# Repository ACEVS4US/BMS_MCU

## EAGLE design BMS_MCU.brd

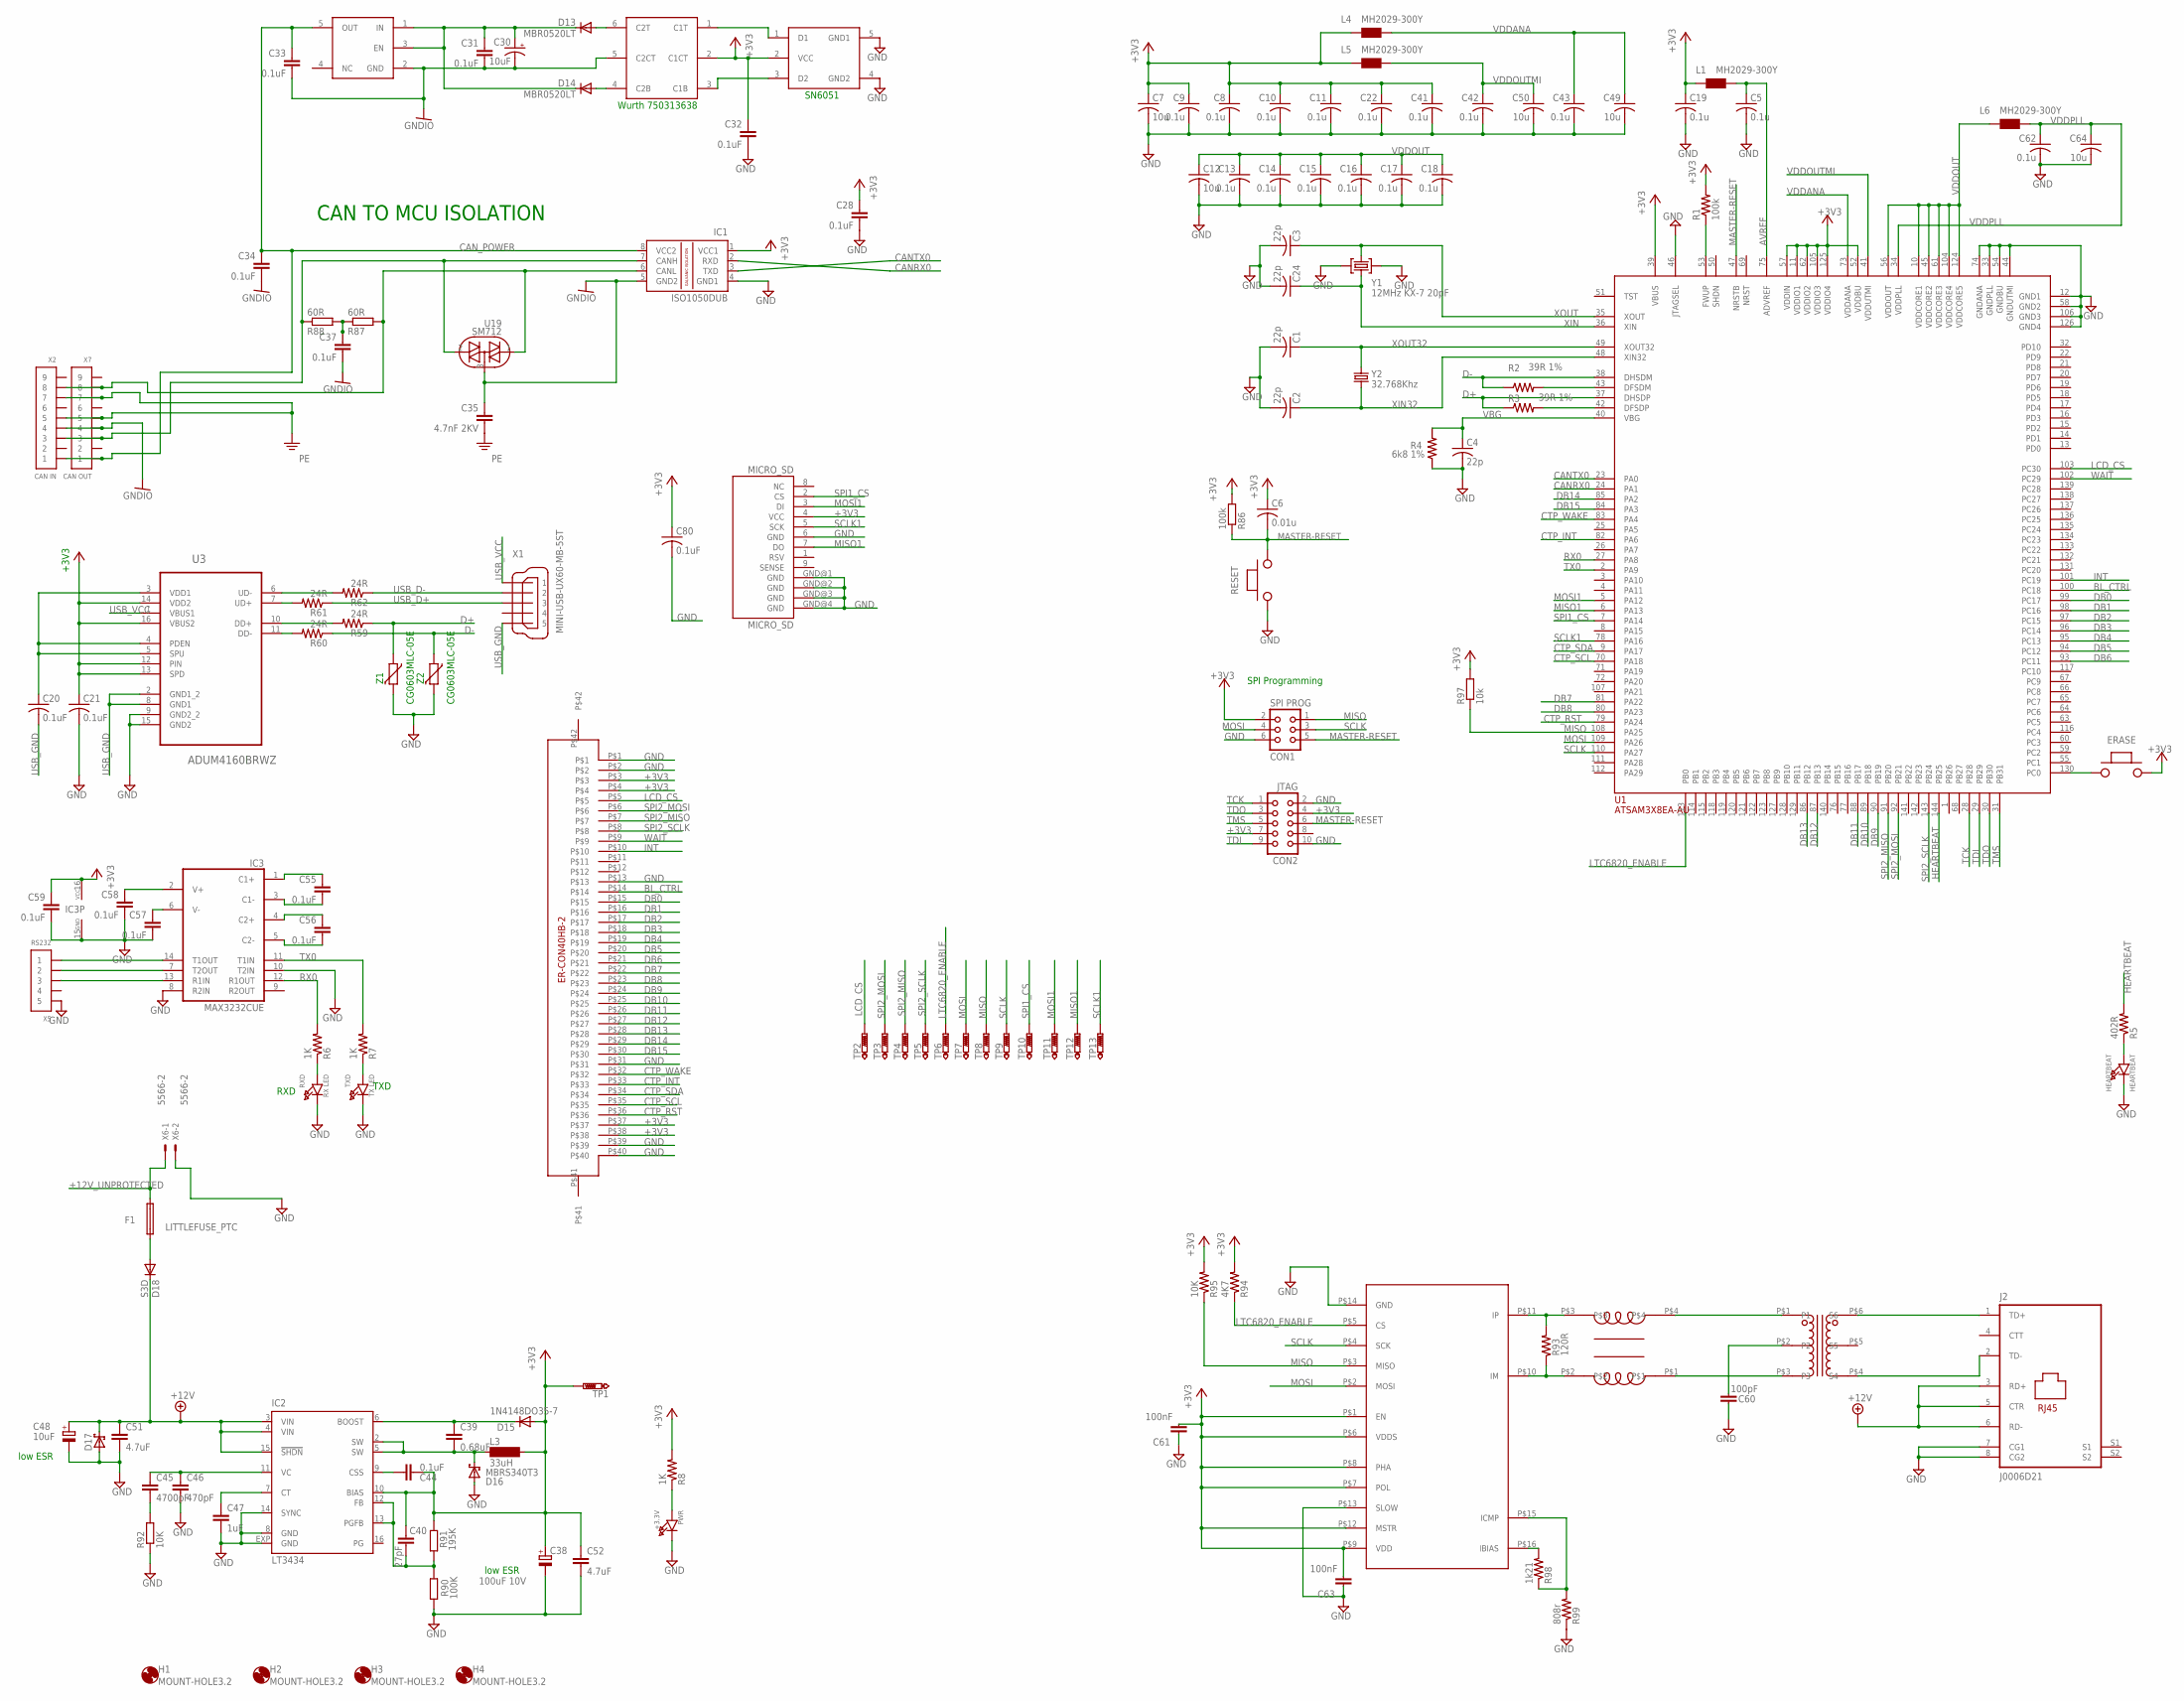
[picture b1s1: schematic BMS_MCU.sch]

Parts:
+3.3V: PWR; CHIPLED_0805
C1, C2, C4: 22p; C0805
C3, C24: 22p; C1206
C5, C8, C9, C10, C11, C13, C14, C15, C16, C17, C18, C19, C22, C41, C42, C43, C62: 0.1u; C0805
C6: 0.01u; C0805
C7, C12, C49, C50, C64: 10u; C0805
C20, C21, C28, C80: 0.1uF; C0805
C30, C48: 10uF; SMC_D
C31, C34, C44, C55, C56, C57, C58, C59: 0.1uF; C0603
C32, C33, C37: 0.1uF; C1206
C35: 4.7nF 2KV; C1206
C38: 100uF 10V; SMC_D
C39: 0.68uF; C0603
C40: 27pF; C0603
C45: 4700pF; C0603
C46: 470pF; C0603
C47: 1uF; C0603
C51, C52: 4.7uF; C1206
C60: 100pF; C1206@1
C61, C63: 100nF; C0603@1
CON1: SPI PROG; CON06
CON2: JTAG; CON10
D13, D14: MBR0520LT; SOD123
D15: 1N4148DO35-7; DO35-7
D16: MBRS340T3; SMC
D17: SCHOTTKY-DIODESMC; SMC
D18: S3D; SMC
ERASE: PUCHBUTTON
F1: LITTLEFUSE_PTC; 1812
H1, H2, H3, H4: MOUNT-HOLE3.2; 3,2
HEARTBEAT: HEARTBEAT; CHIPLED_0805
IC1: ISO1050DUB; DUB-R-PDSO-G8
IC2: LT3434; TSSOP16EXP
IC3: MAX3232CUE; TSSOP16
J2: J0006D21; J0-C/D/E
L1, L4, L5, L6: MH2029-300Y; 0805
L3: 33uH; MS85
MICRO_SD: MICRO_SD; MICROSD_PP
R1: 100k; R0805
R2, R3: 39R 1%; R0805
R4: 6k8 1%; R0805
R5: 402R; R0805
R6, R7, R8: 1K; R0805
R59, R60, R61, R62: 24R; R0805
R86: 100k; R0603
R87, R88: 60R; R0603
R90: 100K; R0603
R91: 195K; R0603
R92, R95: 10K; R0603
R93: 120R; R0603
R94: 4K7; R0603
R97: 10k; R0603
R98: 1k21; R0603
R99: 808r; R0603
RESET: PUCHBUTTON
RXD: RX LED; CHIPLED_0805
TP1, TP2, TP3, TP4, TP5, TP6, TP7, TP8, TP9, TP10, TP11, TP12, TP13: PTR1PAD1-13; P1-13
TXD: TX LED; CHIPLED_0805
U1: ATSAM3X8EA-AU; LQFP144
U2: LTC6820; MSOP16
U3: ADUM4160BRWZ; SOIC127P1032X265-16N
U16: SN6501; SOT23-DBV
U17: WURTHWURTH; TSOT23-6_DDC
U18: TPS76350; SOT23-DBV
U19: SM712; SOT23
U$1: DLW43SH510XK2; DLW43S
U$2: ER-CON40HB-2
U$4: T3001NL
X1: MINI-USB-UX60-MB-5ST; UX60-MB-5ST
X2: CAN IN; PB-53398-09
X5: RS232; CM-502386-05
X6: 5566-2
X7: CAN OUT; PB-53398-09
Y1: 12MHz KX-7 20pF; CRYSTAL-3.2-2.5
Y2: 32.768Khz; ARDUINO_WIFI_SHIELD_V018_TG_RESONATOR_EPSON_FC_145
Z1, Z2: CG0603MLC-05E; CT/CN0603

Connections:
+3V3: C6.1, C7.1, C8.1, C9.1, C10.1, C11.1, C19.1, C21.1, C22.1, C28.1, C32.1, C38.+, C40.1, C41.1, C44.2, C52.1, C59.1, C61.1, C63.1, C80.1, CON1.2, CON2.7, D15.A, ERASE.P$2, IC1.1 (VCC1), IC2.10 (BIAS), IC3.16 (VCC), L1.1, L3.2, L4.1, L5.1, MICRO_SD.4 (VCC), R1.2, R8.2, R86.2, R91.1, R94.2, R95.2, R97.2, TP1.TP, U1.11 (VDDIO1), U1.39 (VBUS), U1.52 (VDDBU), U1.57 (VDDIN), U1.62 (VDDIO2), U1.105 (VDDIO3), U1.125 (VDDIO4), U2.P$1 (EN), U2.P$6 (VDDS), U2.P$7 (POL), U2.P$8 (PHA), U2.P$9 (VDD), U2.P$12 (MSTR), U3.12 (PIN), U3.13 (SPD), U3.14 (VDD2), U3.16 (VBUS2), U16.2 (VCC), U17.2 (C1CT), U$2.P$3, U$2.P$4, U$2.P$37, U$2.P$38
+12V: C48.+, C51.1, D17.C, D18.C, IC2.3 (VIN), IC2.4 (VIN), IC2.15 (!SHDN), J2.3 (RD+), J2.5 (CTR), J2.6 (RD-)
+12V_UNPROTECTED: F1.P$2 (2), X6.1
AVREF: C5.1, L1.2, U1.75 (ADVREF)
BL_CTRL: U1.100 (PC18), U$2.P$14
CANRX0: IC1.2 (RXD), U1.24 (PA1)
CANTX0: IC1.3 (TXD), U1.23 (PA0)
CAN_POWER: C33.1, C34.1, IC1.8 (VCC2), U18.5 (OUT), X2.1, X7.1
CTP_INT: U1.82 (PA6), U$2.P$33
CTP_RST: U1.79 (PA24), U$2.P$36
CTP_SCL: U1.70 (PA18), U$2.P$35
CTP_SDA: U1.9 (PA17), U$2.P$34
CTP_WAKE: U1.83 (PA4), U$2.P$32
D+: R3.1, R59.1, U1.37 (DHSDP), Z1.1
D-: R2.1, R60.1, U1.38 (DHSDM), Z2.1
DB0: U1.99 (PC17), U$2.P$15
DB1: U1.98 (PC16), U$2.P$16
DB2: U1.97 (PC15), U$2.P$17
DB3: U1.96 (PC14), U$2.P$18
DB4: U1.95 (PC13), U$2.P$19
DB5: U1.94 (PC12), U$2.P$20
DB6: U1.93 (PC11), U$2.P$21
DB7: U1.81 (PA22), U$2.P$22
DB8: U1.80 (PA23), U$2.P$23
DB9: U1.90 (PB19), U$2.P$24
DB10: U1.89 (PB18), U$2.P$25
DB11: U1.88 (PB17), U$2.P$26
DB12: U1.87 (PB13), U$2.P$27
DB13: U1.86 (PB12), U$2.P$28
DB14: U1.85 (PA2), U$2.P$29
DB15: U1.84 (PA3), U$2.P$30
ERASE_S: ERASE.P$1, U1.130 (PC0)
GND: +3.3V.C, C1.2, C2.2, C3.2, C4.2, C5.2, C7.2, C8.2, C9.2, C10.2, C11.2, C12.2, C13.2, C14.2, C15.2, C16.2, C17.2, C18.2, C19.2, C21.2, C22.2, C24.2, C28.2, C32.2, C38.-, C41.2, C42.2, C43.2, C46.2, C47.2, C48.-, C49.2, C50.2, C51.2, C52.2, C57.2, C58.2, C59.2, C60.2, C61.2, C62.2, C63.2, C64.2, C80.2, CON1.6, CON2.2, CON2.10, D16.A, D17.A, HEARTBEAT.C, IC1.4 (GND1), IC2.8 (GND), IC2.14 (SYNC), IC2.EXP (GND), IC3.8 (R2IN), IC3.10 (T2IN), IC3.15 (GND), J2.7 (CG1), J2.8 (CG2), MICRO_SD.6 (GND), MICRO_SD.GND@1 (GND), MICRO_SD.GND@2 (GND), MICRO_SD.GND@3 (GND), MICRO_SD.GND@4 (GND), R4.1, R90.1, R92.1, R99.1, RESET.P$1, RXD.C, TXD.C, U1.12 (GND1), U1.33 (GNDPLL), U1.44 (GNDUTMI), U1.46 (JTAGSEL), U1.54 (GNDBU), U1.58 (GND2), U1.74 (GNDANA), U1.106 (GND3), U1.126 (GND4), U2.P$13 (SLOW), U2.P$14 (GND), U3.9 (GND2_2), U3.15 (GND2), U16.4 (GND2), U16.5 (GND1), U$2.P$1, U$2.P$2, U$2.P$13, U$2.P$31, U$2.P$39, U$2.P$40, X5.5, X6.2, Y1.2 (GND), Y1.4 (GND), Z1.2, Z2.2
GNDIO: C30.-, C31.2, C33.2, C34.2, C35.1, C37.2, IC1.5 (GND2), U17.5 (C2CT), U18.2 (GND), U19.3 (T2), X2.4, X7.4
HEARTBEAT: R5.2, U1.144 (PB25)
INT: U1.101 (PC19), U$2.P$10
LCD_CS: TP2.TP, U1.103 (PC30), U$2.P$5
LTC6820_ENABLE: R94.1, TP6.TP, U1.113 (PB0), U2.P$5 (CS)
MASTER-RESET: C6.2, CON1.5, CON2.6, R86.1, RESET.P$2, U1.47 (NRSTB)
MISO: CON1.1, R95.1, R97.1, TP8.TP, U1.108 (PA25), U2.P$3 (MISO)
MISO1: MICRO_SD.7 (DO), TP12.TP, U1.6 (PA13)
MOSI: CON1.4, TP7.TP, U1.109 (PA26), U2.P$2 (MOSI)
MOSI1: MICRO_SD.3 (DI), TP11.TP, U1.5 (PA12)
unnamed: U$1.P$4, U$4.P$1 (P1)
unnamed: U$1.P$1, U$4.P$3 (P3)
unnamed: +3.3V.A, R8.1
unnamed: J2.2 (TD-), U$4.P$4 (S4)
unnamed: J2.1 (TD+), U$4.P$6 (S6)
unnamed: HEARTBEAT.A, R5.1
unnamed: C20.1, U3.3 (VDD1), U3.4 (PDEN), U3.5 (SPU)
unnamed: U16.1 (D1), U17.1 (C1T)
unnamed: D13.A, U17.6 (C2T)
unnamed: R62.2, U3.6 (UD-)
unnamed: R61.2, U3.7 (UD+)
unnamed: R6.1, RXD.A
unnamed: R7.1, TXD.A
unnamed: C30.+, C31.1, D13.C, D14.C, U18.1 (IN), U18.3 (EN)
unnamed: D14.A, U17.4 (C2B)
unnamed: R59.2, U3.10 (DD+)
unnamed: R60.2, U3.11 (DD-)
unnamed: R93.2, U2.P$11 (IP), U$1.P$3
unnamed: R2.2, U1.43 (DFSDM)
unnamed: IC1.6 (CANL), R87.2, U19.1 (T1), X2.8, X7.8
unnamed: IC1.7 (CANH), R88.1, U19.2 (T3), X2.3, X7.3
unnamed: R3.2, U1.42 (DFSDP)
unnamed: R1.1, U1.53 (FWUP)
unnamed: C40.2, IC2.12 (FB), IC2.13 (PGFB), R90.2, R91.2
unnamed: C55.1, IC3.1 (C1+)
unnamed: C55.2, IC3.3 (C1-)
unnamed: C56.1, IC3.4 (C2+)
unnamed: R93.1, U2.P$10 (IM), U$1.P$2
unnamed: C60.1, U$4.P$2 (P2)
unnamed: C56.2, IC3.5 (C2-)
unnamed: U16.3 (D2), U17.3 (C1B)
unnamed: C57.1, IC3.6 (V-)
unnamed: C37.1, R87.1, R88.2
unnamed: C39.1, D15.C, IC2.6 (BOOST)
unnamed: C44.1, IC2.9 (CSS)
unnamed: C39.2, D16.C, IC2.2 (SW), IC2.5 (SW), L3.1
unnamed: C47.1, IC2.7 (CT)
unnamed: C45.1, C46.1, IC2.11 (VC)
unnamed: C45.2, R92.2
unnamed: D18.A, F1.P$1 (1)
unnamed: IC3.14 (T1OUT), X5.1
unnamed: IC3.7 (T2OUT), X5.2
unnamed: IC3.13 (R1IN), X5.3
unnamed: C58.1, IC3.2 (V+)
unnamed: R98.1, R99.2, U2.P$15 (ICMP)
unnamed: R98.2, U2.P$16 (IBIAS)
PE: C35.2, X2.5, X2.7, X7.5, X7.7
RX0: IC3.12 (R1OUT), R6.2, U1.27 (PA8)
SCLK: CON1.3, TP9.TP, U1.110 (PA27), U2.P$4 (SCK)
SCLK1: MICRO_SD.5 (SCK), TP13.TP, U1.78 (PA16)
SPI1_CS: MICRO_SD.2 (CS), TP10.TP, U1.7 (PA14)
SPI2_MISO: TP4.TP, U1.91 (PB20), U$2.P$7
SPI2_MOSI: TP3.TP, U1.92 (PB21), U$2.P$6
SPI2_SCLK: TP5.TP, U1.143 (PB24), U$2.P$8
TCK: CON2.1, U1.28 (PB28)
TDI: CON2.9, U1.29 (PB29)
TDO: CON2.3, U1.30 (PB30)
TMS: CON2.5, U1.31 (PB31)
TX0: IC3.11 (T1IN), R7.2, U1.2 (PA9)
USB_D+: R61.1, X1.3
USB_D-: R62.1, X1.2
USB_GND: C20.2, U3.2 (GND1_2), U3.8 (GND1), X1.5
USB_VCC: U3.1 (VBUS1), X1.1
VBG: C4.1, R4.2, U1.40 (VBG)
VDDANA: C43.1, C49.1, L4.2, U1.73 (VDDANA)
VDDOUT: C12.1, C13.1, C14.1, C15.1, C16.1, C17.1, C18.1, L6.1, U1.10 (VDDCORE1), U1.45 (VDDCORE2), U1.56 (VDDOUT), U1.61 (VDDCORE3), U1.104 (VDDCORE4), U1.124 (VDDCORE5)
VDDOUTMI: C42.1, C50.1, L5.2, U1.41 (VDDUTMI)
VDDPLL: C62.1, C64.1, L6.2, U1.34 (VDDPLL)
WAIT: U1.102 (PC29), U$2.P$9
XIN: C24.1, U1.36 (XIN), Y1.1 (C1)
XIN32: C2.1, U1.48 (XIN32), Y2.P$2 (2)
XOUT: C3.1, U1.35 (XOUT), Y1.3 (C2)
XOUT32: C1.1, U1.49 (XOUT32), Y2.P$1 (1)

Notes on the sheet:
SN6051
Wurth 750313638
CAN TO MCU ISOLATION
low ESR
RXD
TXD
SPI Programming

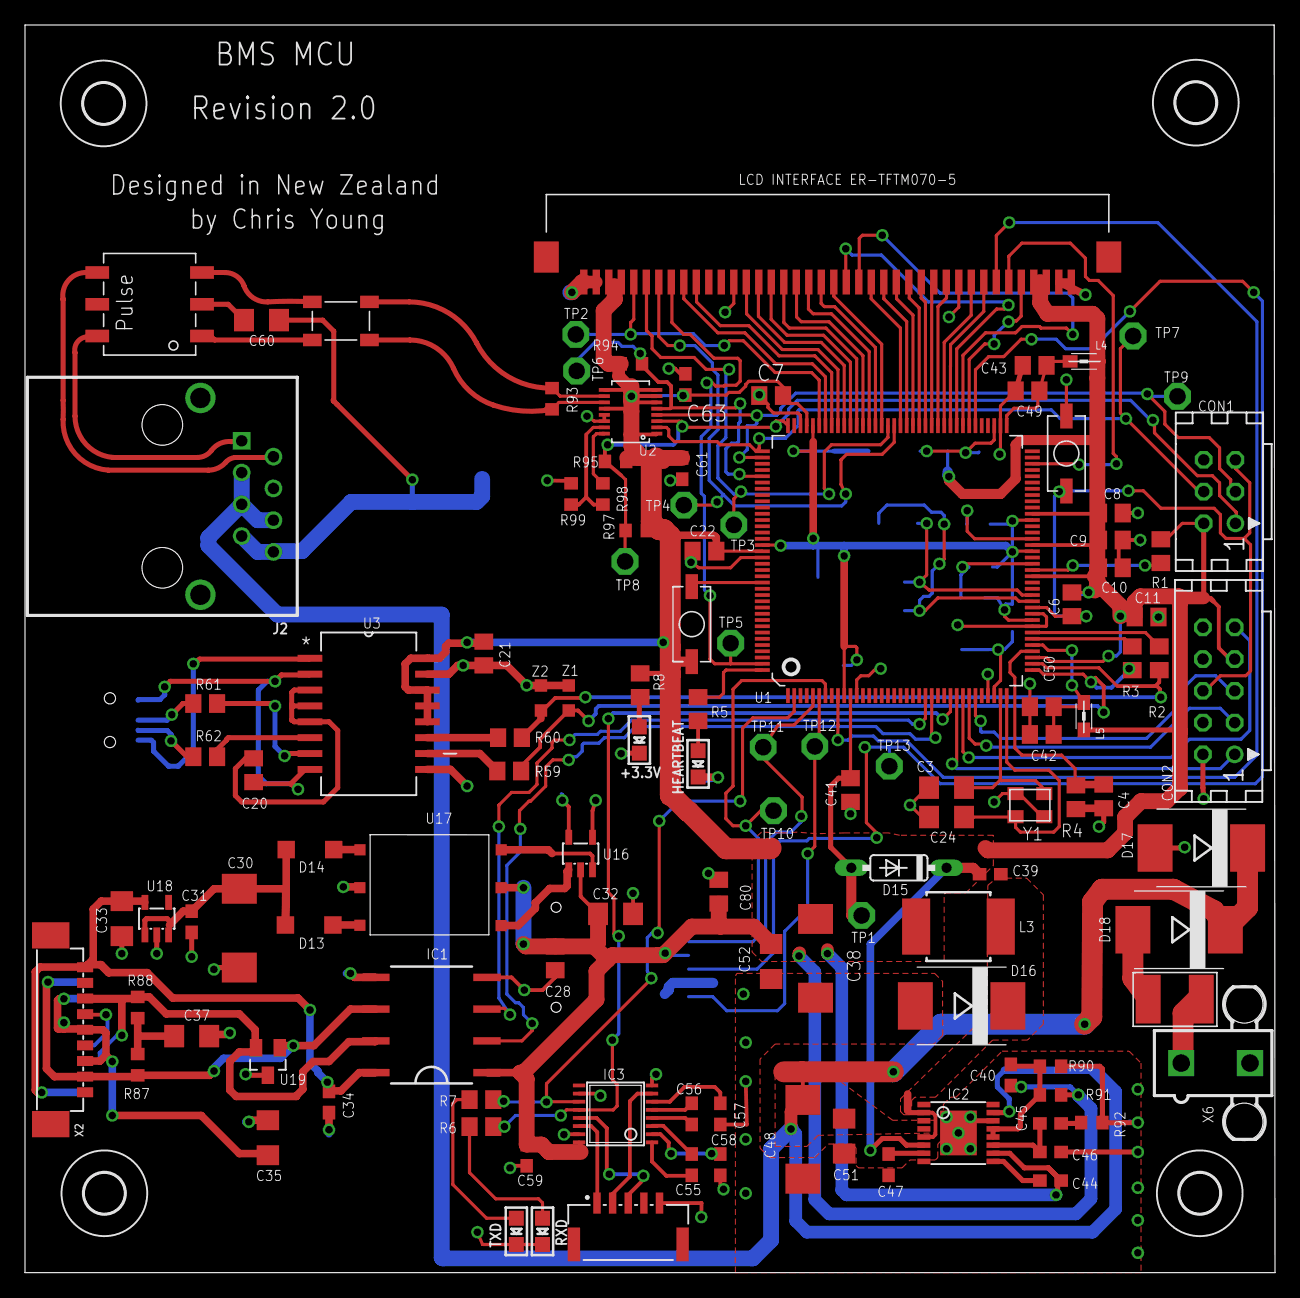
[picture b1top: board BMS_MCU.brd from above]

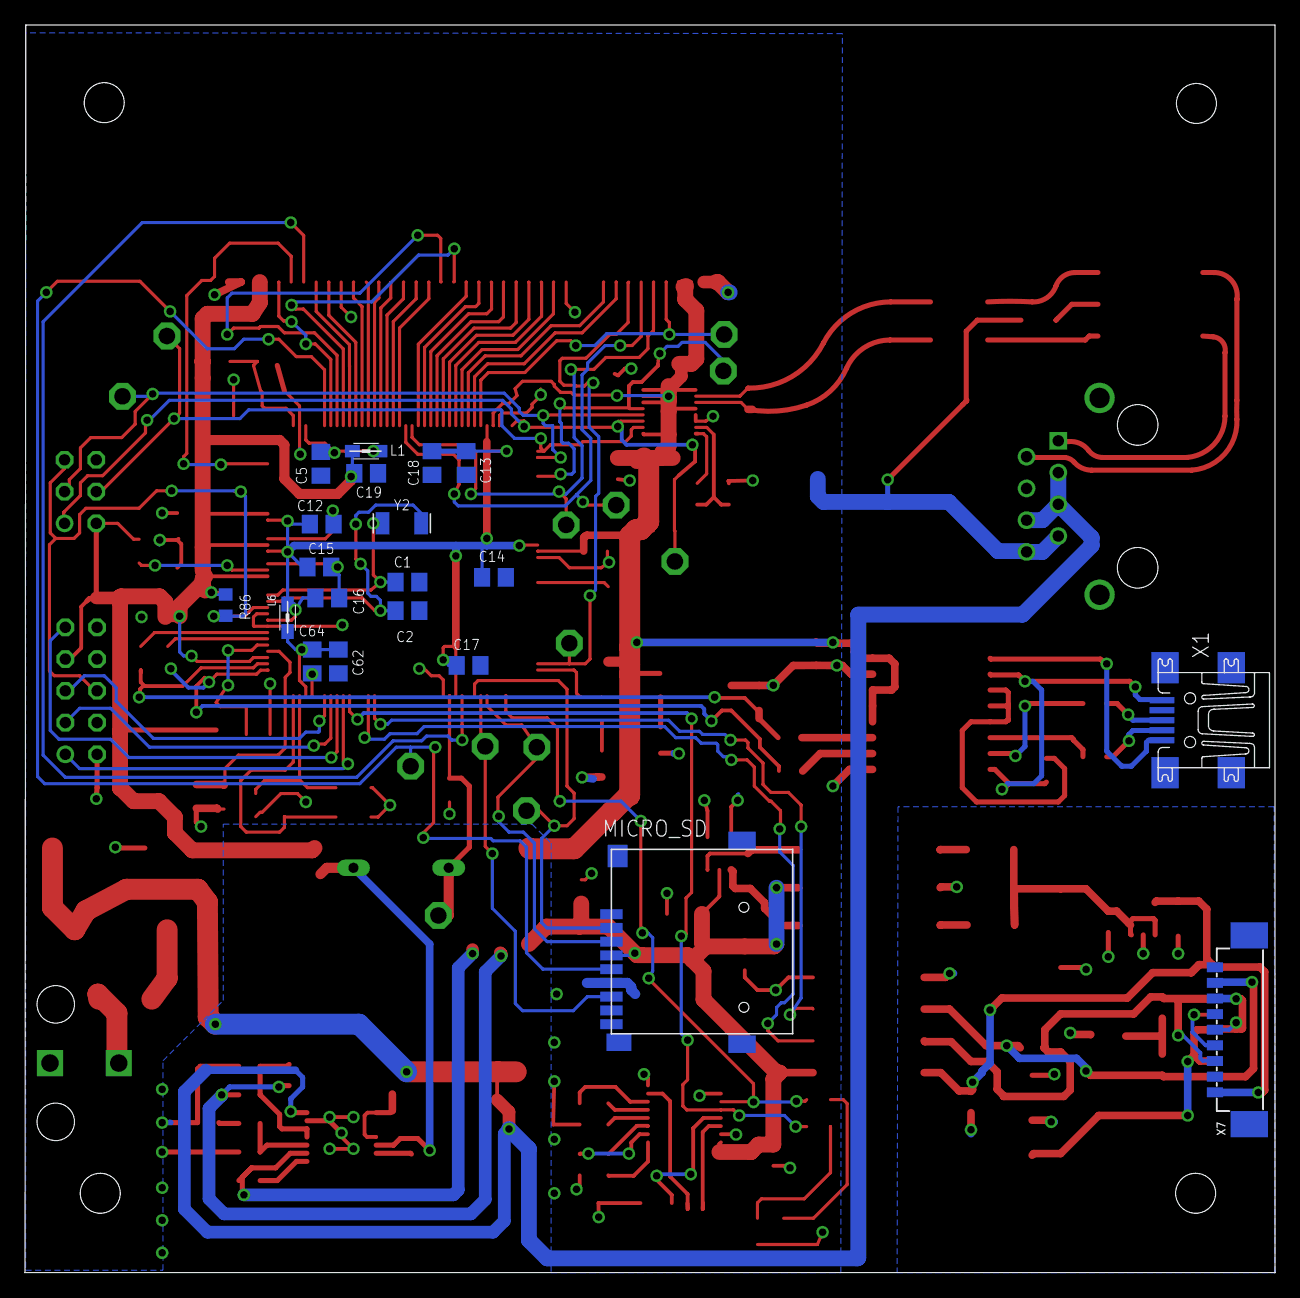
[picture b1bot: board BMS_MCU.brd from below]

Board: 2 copper layers, 100.0 x 99.8 mm, 142 parts (20 on the bottom side), 116 nets.

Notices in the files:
parts and their libraries:
pulse-eng: Copyright (C) 2008, Bob Starr
microbuilder: This work is placed in the public domain, and may be freely used for commercial and non-commercial work with the following conditions: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
